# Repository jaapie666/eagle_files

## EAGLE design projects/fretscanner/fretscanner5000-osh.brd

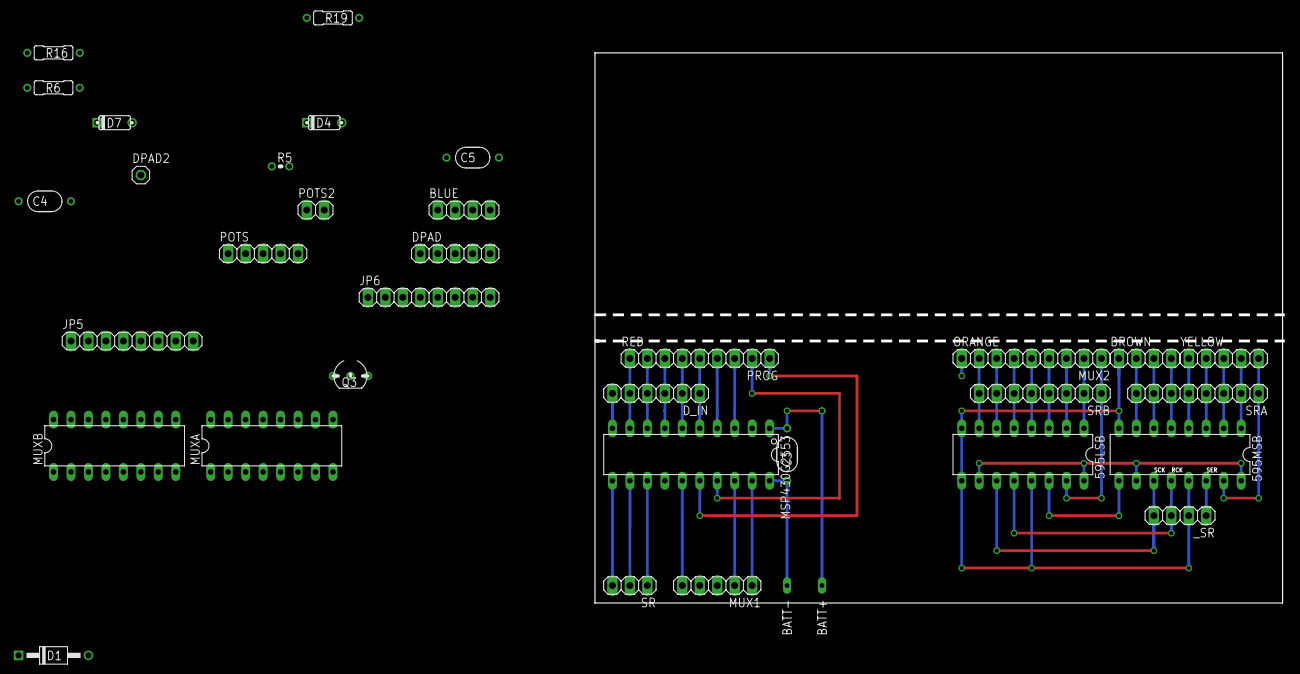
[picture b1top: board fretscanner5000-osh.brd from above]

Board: 2 copper layers, 100.0 x 80.0 mm, 37 parts (0 on the bottom side), 50 nets.

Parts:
595LSB, 595MSB: 74LS595N; DIL16
BATT+: LONG
BATT-: LONG
BLUE: 1X04
BROWN: 1X04
C3, C4, C5: 100n; 050X030_050_3
D1: DO41-4
D4, D7: 1N4148-2; DO35-2
DPAD: 1X05
DPAD2: 1X01
D_IN: 1X06
JP5, JP6: 1X08
MSP430G2553: G2XX3---N20; N20
MUX1: 1X05
MUX2: 1X04
MUXA: 4051N; DIL16
MUXB: 4051N; DIL16
ORANGE: 1X05
POTS: 1X05
POTS2: 1X02
PROG: 1X04
Q3: 2N3904; TO92-
R5: 300k; R0207/1V
R6: 1k; R0207/3
R16, R19: 30k; R0207/3
RED: 1X05
SR: 1X03
SRA: 1X08
SRB: 1X08
YELLOW: 1X05
_SR: 1X04

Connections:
D0: D_IN.1, MSP430G2553.5, RED.5
D1: D_IN.2, MSP430G2553.6, RED.4
D2: D_IN.3, MSP430G2553.7, RED.3
D3: D_IN.4, MSP430G2553.8, RED.2
D4: D_IN.5, MSP430G2553.9, RED.1
D5: D_IN.6, MSP430G2553.10, ORANGE.1
GND: 595LSB.8, 595LSB.13, 595MSB.8, 595MSB.13, BATT-.1, BROWN.1, C3.1, MSP430G2553.20
INH_A: MSP430G2553.18, MUX1.2
INH_B: MSP430G2553.19, MUX1.1
M_F1: 595MSB.1, SRA.2, YELLOW.4
M_F2: 595MSB.2, SRA.3, YELLOW.3
M_F3: 595MSB.3, SRA.4, YELLOW.2
M_F4: 595MSB.4, SRA.5, YELLOW.1
M_F5: 595LSB.4, ORANGE.5, SRB.5
M_F6: 595LSB.5, ORANGE.4, SRB.6
M_F7: 595LSB.6, ORANGE.3, SRB.7
M_F8: 595LSB.7, ORANGE.2, SRB.8
M_F9: 595MSB.5, BROWN.4, SRA.6
M_F10: 595MSB.15, SRA.1, YELLOW.5
M_F11: 595MSB.6, BROWN.3, SRA.7
M_F12: 595MSB.7, BROWN.2, SRA.8
unnamed: 595LSB.14, 595MSB.9
unnamed: 595LSB.15, MUX2.1, SRB.1
unnamed: 595LSB.1, MUX2.2, SRB.2
unnamed: 595LSB.2, MUX2.3, SRB.3
unnamed: Q3.2, R5.1, R6.2
unnamed: 595LSB.3, MUX2.4, SRB.4
unnamed: C5.1, MUXA.16
unnamed: D4.A, R16.2
unnamed: C4.1, MUXB.16
unnamed: D4.C, D7.C, R6.1
unnamed: C4.2, MUXB.7, MUXB.8
unnamed: C5.2, MUXA.7, MUXA.8
unnamed: Q3.3, R5.2
unnamed: D7.A, R19.2
unnamed: MSP430G2553.15, MUX1.5
unnamed: 595MSB.14, _SR.1
unnamed: 595LSB.11, 595MSB.11, _SR.4
unnamed: 595LSB.12, 595MSB.12, _SR.3
RCK: MSP430G2553.13, SR.1
RXD: MSP430G2553.3, PROG.3
SCK: MSP430G2553.12, SR.2
SER: MSP430G2553.11, SR.3
SR0: MUXA.11, MUXB.11
SR1: MUXA.10, MUXB.10
SR2: MUXA.9, MUXB.9
TEST: MSP430G2553.17, PROG.2
TXD: MSP430G2553.4, PROG.4
VA: 595LSB.10, 595LSB.16, 595MSB.10, 595MSB.16, BATT+.1, C3.2, MSP430G2553.1
_RST: MSP430G2553.16, PROG.1

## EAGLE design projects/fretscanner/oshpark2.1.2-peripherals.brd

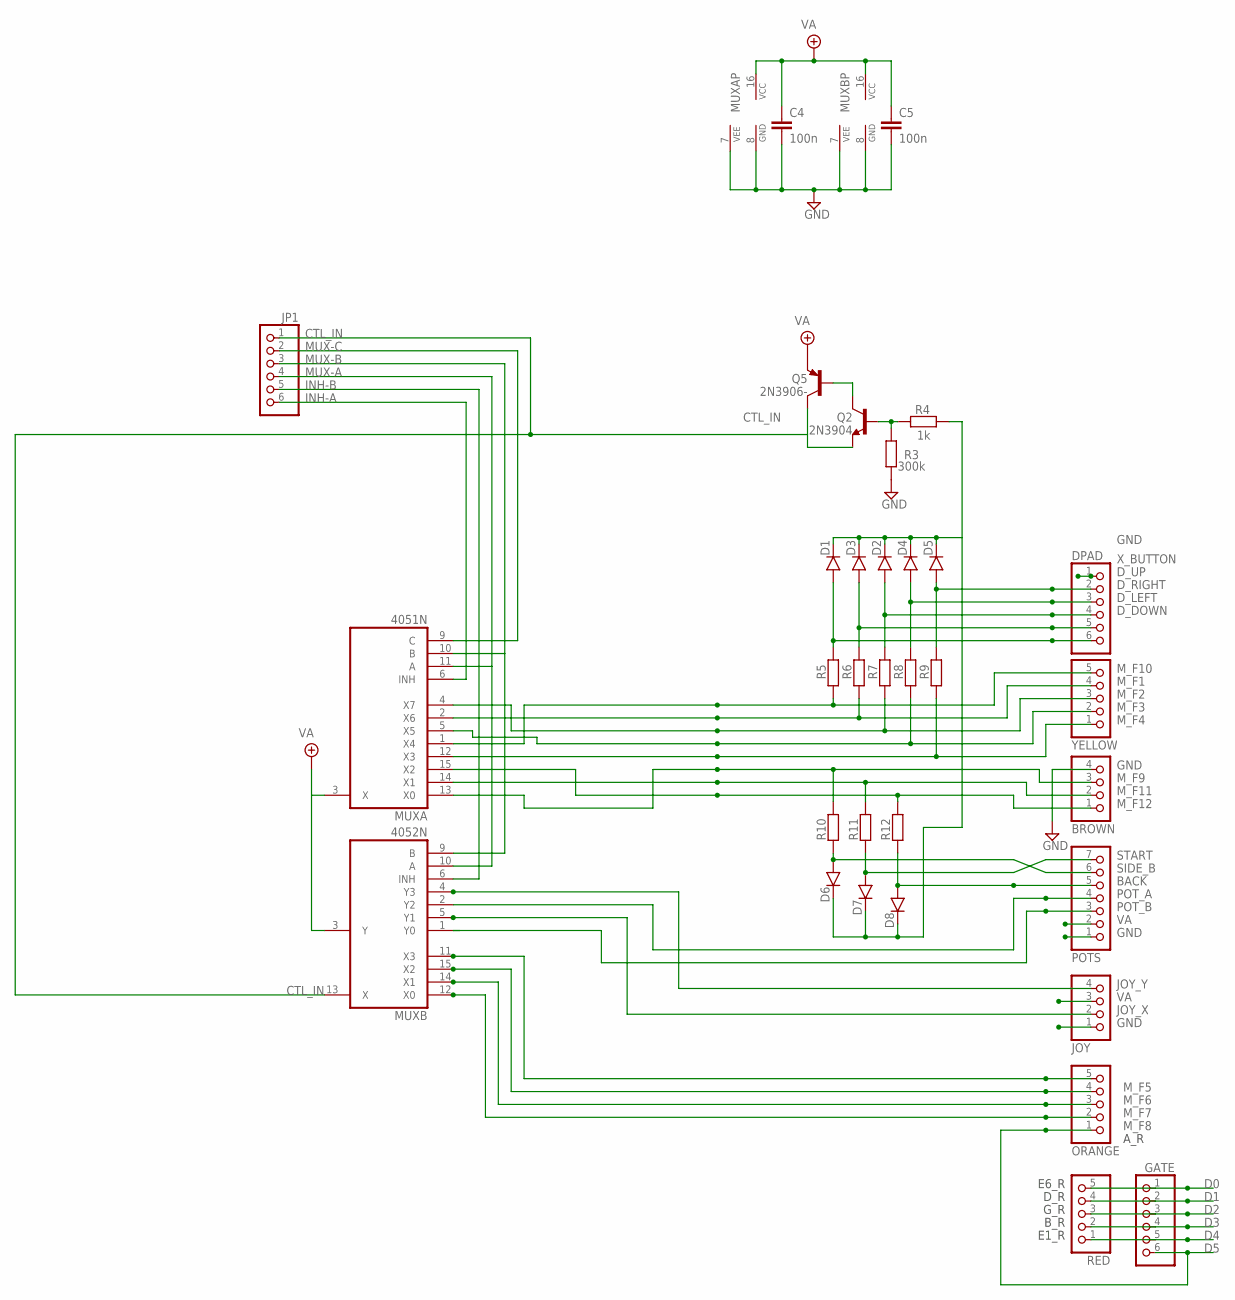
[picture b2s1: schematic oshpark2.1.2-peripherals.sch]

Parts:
BROWN: PINHD-1X4; 1X04
C4: 100n; 050X030_050_1
C5: 100n; 050X030_050_3
D1, D2, D3, D4, D5, D6, D7, D8: 1N4148-2; DO35-2
DPAD: PINHD-1X6; 1X06
GATE: PINHD-1X6; 1X06
JOY: PINHD-1X4; 1X04
JP1: PINHD-1X6; 1X06
MUXA: 4051N; DIL16
MUXB: 4052N; DIL16
ORANGE: PINHD-1X5; 1X05
POTS: PINHD-1X7; 1X07
Q2: 2N3904; TO92-
Q5: 2N3906-; TO92-
R3: 300k; R0207/1V
R4: 1k; R0207/3
R5, R6, R7, R8, R9: 30k; R0207/1V
R10, R11, R12: 30k; R0207/2V
RED: PINHD-1X5; 1X05
YELLOW: PINHD-1X5; 1X05

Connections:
BACK: D7.A, POTS.7, R11.2
CTL_IN: JP1.1, MUXB.13 (X), Q2.3 (E), Q5.1 (C)
D0: GATE.1, RED.5
D1: GATE.2, RED.4
D2: GATE.3, RED.3
D3: GATE.4, RED.2
D4: GATE.5, RED.1
D5: GATE.6, ORANGE.1
D_DOWN: D1.A, DPAD.6, R5.2
D_LEFT: D3.A, DPAD.5, R6.2
D_RIGHT: D2.A, DPAD.4, R7.2
D_UP: D4.A, DPAD.3, R8.2
GND: BROWN.4, C4.2, C5.2, DPAD.1, JOY.1, MUXA.7 (VEE), MUXA.8 (GND), MUXB.7 (VEE), MUXB.8 (GND), POTS.1, R3.2
INH-A: JP1.6, MUXA.6 (INH)
INH-B: JP1.5, MUXB.6 (INH)
JOY_X: JOY.2, MUXB.5 (Y1)
JOY_Y: JOY.4, MUXB.4 (Y3)
MUX-A: JP1.4, MUXA.11 (A), MUXB.10 (A)
MUX-B: JP1.3, MUXA.10 (B), MUXB.9 (B)
MUX-C: JP1.2, MUXA.9 (C)
M_F1: MUXA.2 (X6), R6.1, YELLOW.4
M_F2: MUXA.4 (X7), R7.1, YELLOW.3
M_F3: MUXA.5 (X5), R8.1, YELLOW.2
M_F4: MUXA.12 (X3), R9.1, YELLOW.1
M_F5: MUXB.11 (X3), ORANGE.5
M_F6: MUXB.15 (X2), ORANGE.4
M_F7: MUXB.14 (X1), ORANGE.3
M_F8: MUXB.12 (X0), ORANGE.2
M_F9: BROWN.3, MUXA.13 (X0), R10.1
M_F10: MUXA.1 (X4), R5.1, YELLOW.5
M_F11: BROWN.2, MUXA.14 (X1), R11.1
M_F12: BROWN.1, MUXA.15 (X2), R12.1
unnamed: Q2.1 (C), Q5.2 (B)
unnamed: Q2.2 (B), R3.1, R4.2
unnamed: D1.C, D2.C, D3.C, D4.C, D5.C, D6.C, D7.C, D8.C, R4.1
POT_A: MUXB.2 (Y2), POTS.4
POT_B: MUXB.1 (Y0), POTS.3
SIDE_B: D6.A, POTS.6, R10.2
START: D8.A, POTS.5, R12.2
VA: C4.1, C5.1, JOY.3, MUXA.3 (X), MUXA.16 (VCC), MUXB.3 (Y), MUXB.16 (VCC), POTS.2, Q5.3 (E)
X_BUTTON: D5.A, DPAD.2, R9.2

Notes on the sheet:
E6_R
D_R
G_R
B_R
E1_R
A_R

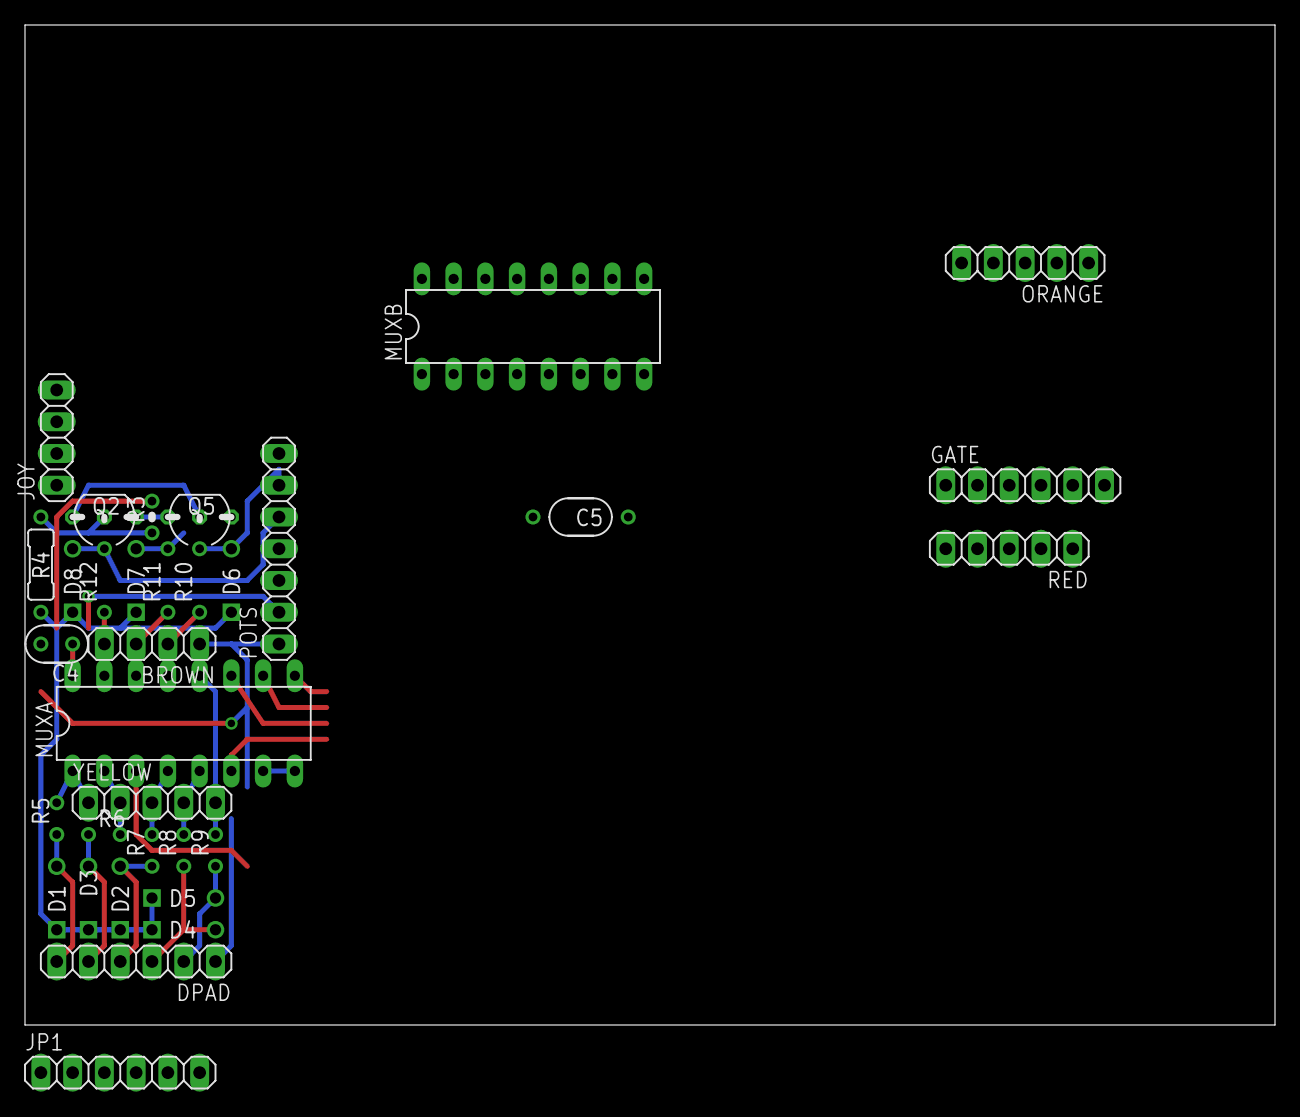
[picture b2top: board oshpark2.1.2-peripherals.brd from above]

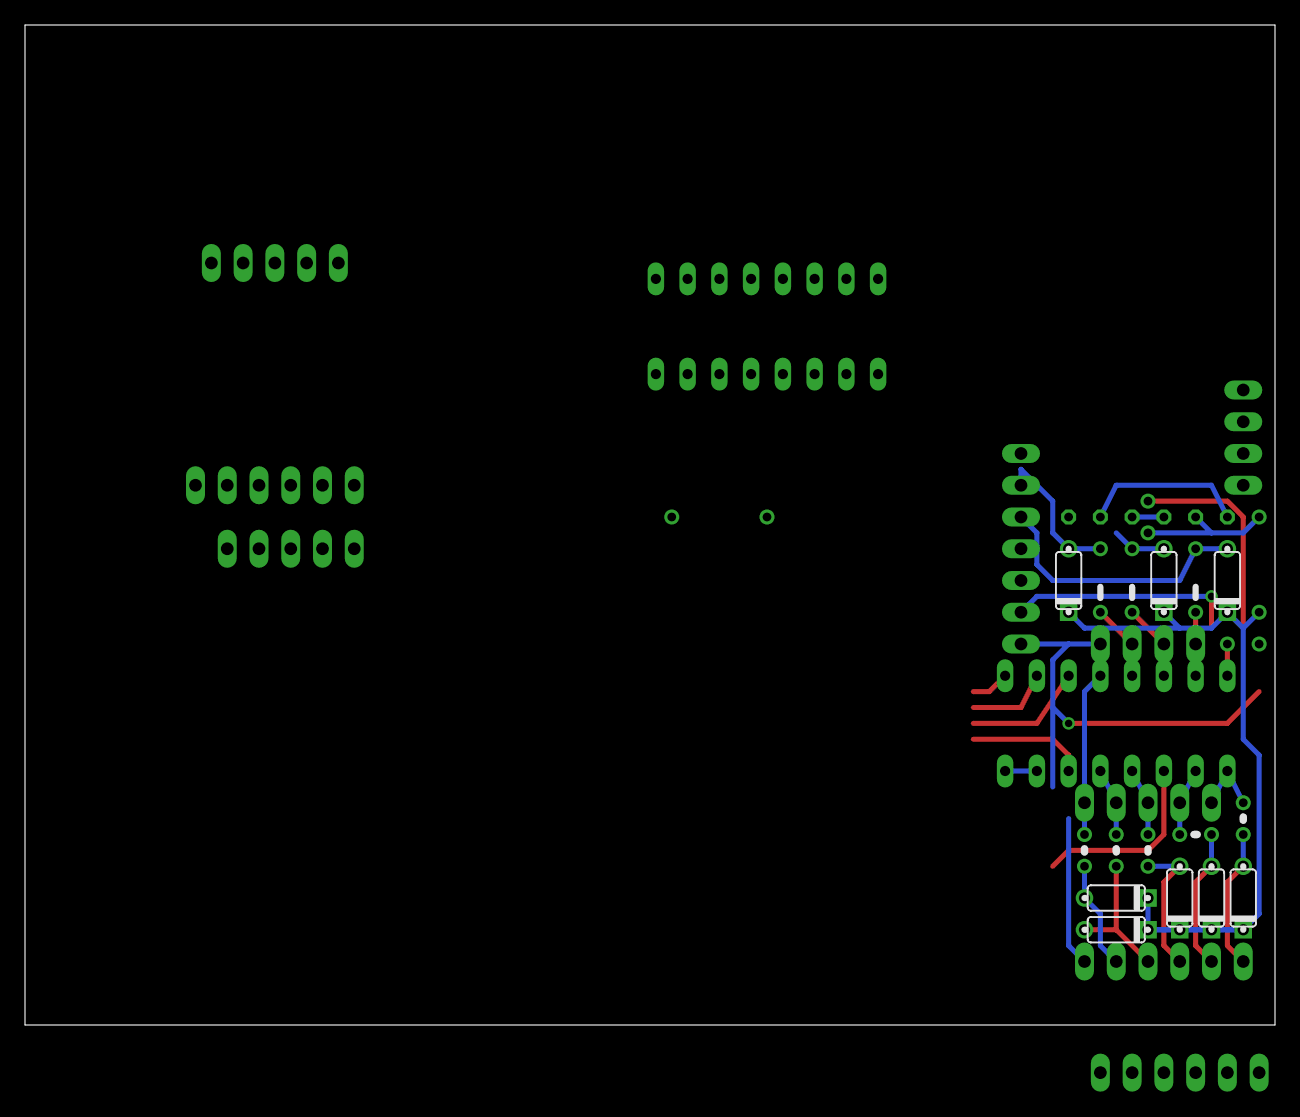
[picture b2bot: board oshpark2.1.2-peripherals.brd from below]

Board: 2 copper layers, 100.0 x 80.0 mm, 33 parts (16 on the bottom side), 41 nets.

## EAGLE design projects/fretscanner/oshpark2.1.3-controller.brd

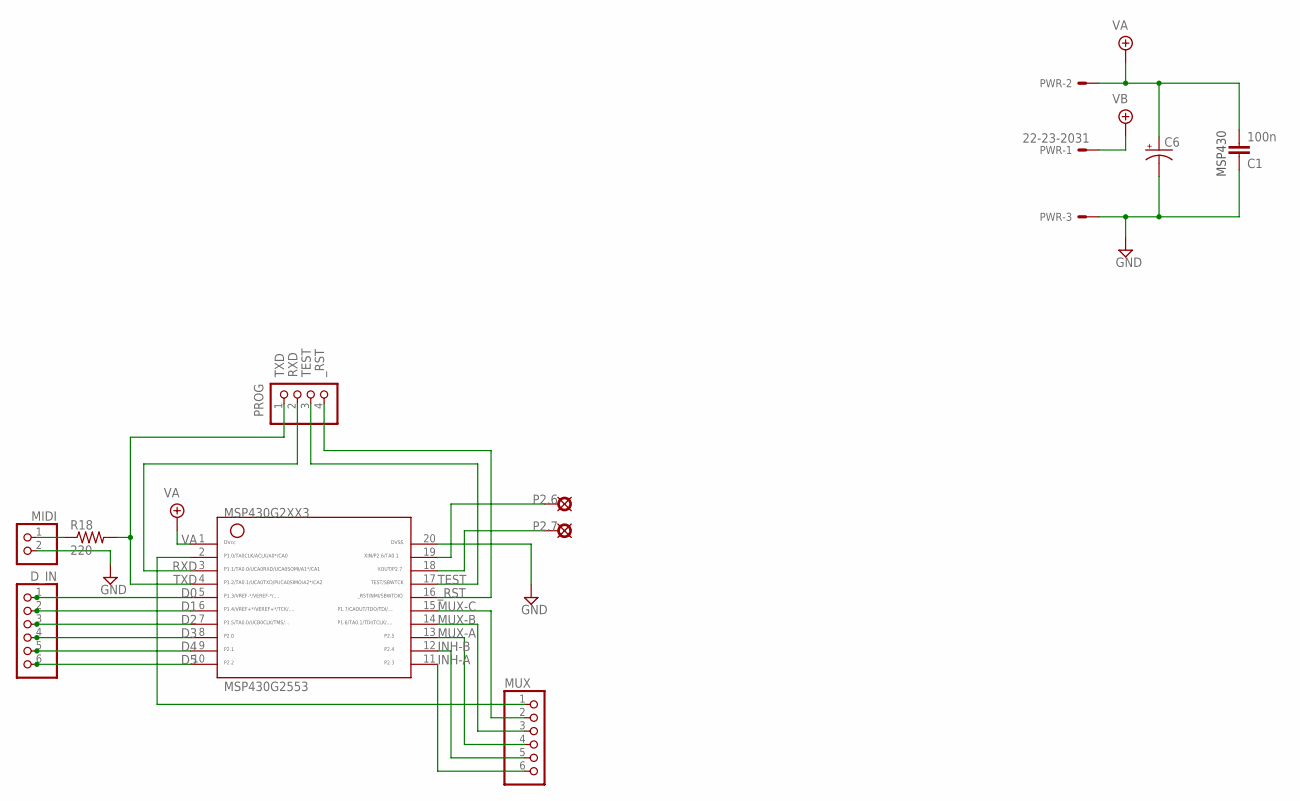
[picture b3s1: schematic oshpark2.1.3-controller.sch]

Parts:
C1: 100n; 050X030_050_3
C6: 0503; 050_020_3
D_IN: PINHD-1X6; 1X06
MIDI: PINHD-1X2; 1X02
MSP430G2553: G2XX3---N20; N20
MUX: PINHD-1X6; 1X06
P2.6, P2.7: PAD; SQUARE
PROG: PINHD-1X4; 1X04
PWR: 22-23-2031
R18: 220; R0207/3

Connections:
D0: D_IN.1, MSP430G2553.5
D1: D_IN.2, MSP430G2553.6
D2: D_IN.3, MSP430G2553.7
D3: D_IN.4, MSP430G2553.8
D4: D_IN.5, MSP430G2553.9
D5: D_IN.6, MSP430G2553.10
GND: C1.1, C6.-, MIDI.2, MSP430G2553.20, PWR.3
INH-A: MSP430G2553.11, MUX.6
INH-B: MSP430G2553.12, MUX.5
MUX-A: MSP430G2553.13, MUX.4
MUX-B: MSP430G2553.14, MUX.3
MUX-C: MSP430G2553.15, MUX.2
unnamed: MIDI.1, R18.1
unnamed: MSP430G2553.2, MUX.1
unnamed: MSP430G2553.19, P2.6.1
unnamed: MSP430G2553.18, P2.7.1
RXD: MSP430G2553.3, PROG.2
TEST: MSP430G2553.17, PROG.3
TXD: MSP430G2553.4, PROG.1, R18.2
VA: C1.2, C6.+, MSP430G2553.1, PWR.2
VB: PWR.1
_RST: MSP430G2553.16, PROG.4

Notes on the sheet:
MSP430

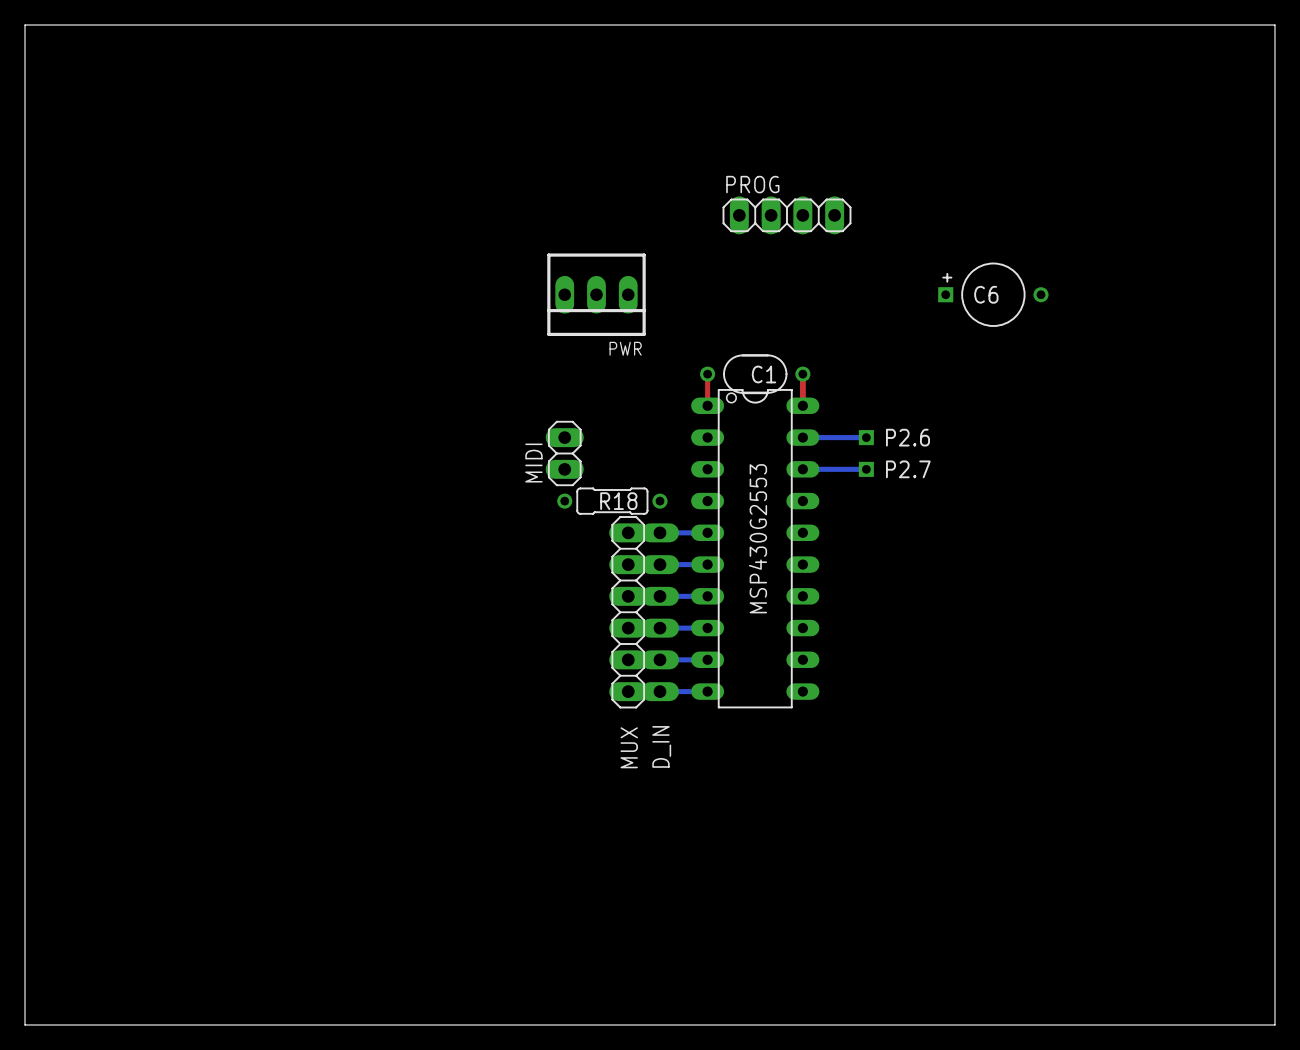
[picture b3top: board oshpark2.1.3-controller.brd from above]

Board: 2 copper layers, 100.0 x 80.0 mm, 11 parts (1 on the bottom side), 21 nets.

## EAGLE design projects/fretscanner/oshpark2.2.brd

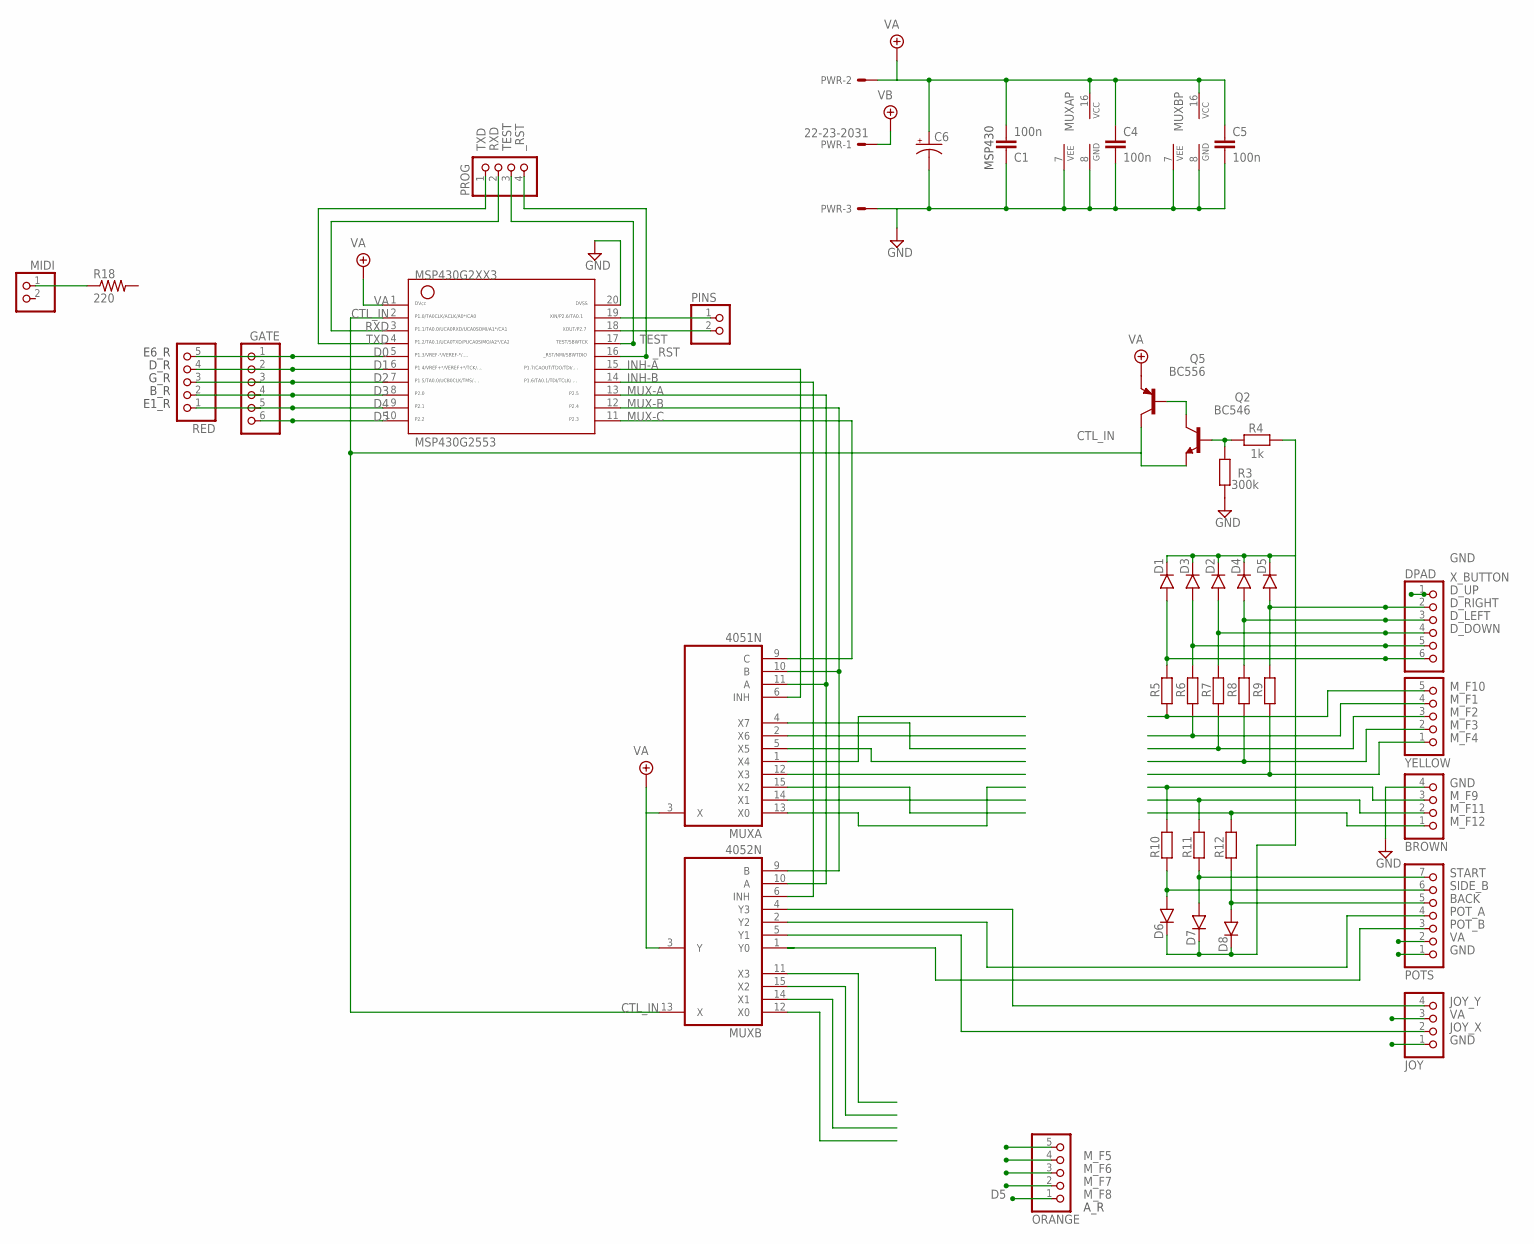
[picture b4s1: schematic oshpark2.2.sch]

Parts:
BROWN: PINHD-1X4; 1X04
C1, C5: 100n; 050X030_050_3
C4: 100n; 050X030_050_1
C6: 0501; 050_020_1
D1, D2, D3, D4, D5, D6, D7, D8: 1N4148-2; DO35-2
DPAD: PINHD-1X6; 1X06
GATE: PINHD-1X6; 1X06
JOY: PINHD-1X4; 1X04
MIDI: PINHD-1X2; 1X02
MSP430G2553: G2XX3---N20; N20
MUXA: 4051N; DIL16
MUXB: 4052N; DIL16
ORANGE: PINHD-1X5; 1X05
PINS: PINHD-1X2; 1X02
POTS: PINHD-1X7; 1X07
PROG: PINHD-1X4; 1X04
PWR: 22-23-2031
Q2: BC546; TO92-EBC
Q5: BC556; TO92-EBC
R3: 300k; R0207/1V
R4: 1k; R0207/3
R5, R6, R7, R8, R9: 30k; R0207/1V
R10, R11, R12: 30k; R0207/2V
R18: 220; R0207/3
RED: PINHD-1X5; 1X05
YELLOW: PINHD-1X5; 1X05

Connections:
BACK: D7.A, POTS.7, R11.2
CTL_IN: MSP430G2553.2, MUXB.13 (X), Q2.E, Q5.C
D0: GATE.1, MSP430G2553.5, RED.5
D1: GATE.2, MSP430G2553.6, RED.4
D2: GATE.3, MSP430G2553.7, RED.3
D3: GATE.4, MSP430G2553.8, RED.2
D4: GATE.5, MSP430G2553.9, RED.1
D5: GATE.6, MSP430G2553.10, ORANGE.1
D_DOWN: D1.A, DPAD.6, R5.2
D_LEFT: D3.A, DPAD.5, R6.2
D_RIGHT: D2.A, DPAD.4, R7.2
D_UP: D4.A, DPAD.3, R8.2
GND: BROWN.4, C1.1, C4.2, C5.2, C6.-, DPAD.1, JOY.1, MSP430G2553.20, MUXA.7 (VEE), MUXA.8 (GND), MUXB.7 (VEE), MUXB.8 (GND), POTS.1, PWR.3, R3.2
INH-A: MSP430G2553.15, MUXA.6 (INH)
INH-B: MSP430G2553.14, MUXB.6 (INH)
JOY_X: JOY.2, MUXB.5 (Y1)
JOY_Y: JOY.4, MUXB.4 (Y3)
MUX-A: MSP430G2553.13, MUXA.11 (A), MUXB.10 (A)
MUX-B: MUXA.10 (B), MUXB.9 (B)
MUX-C: MUXA.9 (C)
M_F1: R6.1, YELLOW.4
M_F2: R7.1, YELLOW.3
M_F3: R8.1, YELLOW.2
M_F4: R9.1, YELLOW.1
M_F5: ORANGE.5
M_F6: ORANGE.4
M_F7: ORANGE.3
M_F8: ORANGE.2
M_F9: BROWN.3, R10.1
M_F10: R5.1, YELLOW.5
M_F11: BROWN.2, R11.1
M_F12: BROWN.1, R12.1
unnamed: MIDI.1, R18.1
unnamed: Q2.C, Q5.B
unnamed: Q2.B, R3.1, R4.2
unnamed: MSP430G2553.19, PINS.1
unnamed: MSP430G2553.18, PINS.2
unnamed: D1.C, D2.C, D3.C, D4.C, D5.C, D6.C, D7.C, D8.C, R4.1
POT_A: MUXB.2 (Y2), POTS.4
POT_B: MUXB.1 (Y0), POTS.3
RXD: MSP430G2553.3, PROG.2
SIDE_B: D6.A, POTS.6, R10.2
START: D8.A, POTS.5, R12.2
TEST: MSP430G2553.17, PROG.3
TXD: MSP430G2553.4, PROG.1
VA: C1.2, C4.1, C5.1, C6.+, JOY.3, MSP430G2553.1, MUXA.3 (X), MUXA.16 (VCC), MUXB.3 (Y), MUXB.16 (VCC), POTS.2, PWR.2, Q5.E
VB: PWR.1
X_BUTTON: D5.A, DPAD.2, R9.2
_RST: MSP430G2553.16, PROG.4

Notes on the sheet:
E6_R
D_R
G_R
B_R
E1_R
A_R
MSP430

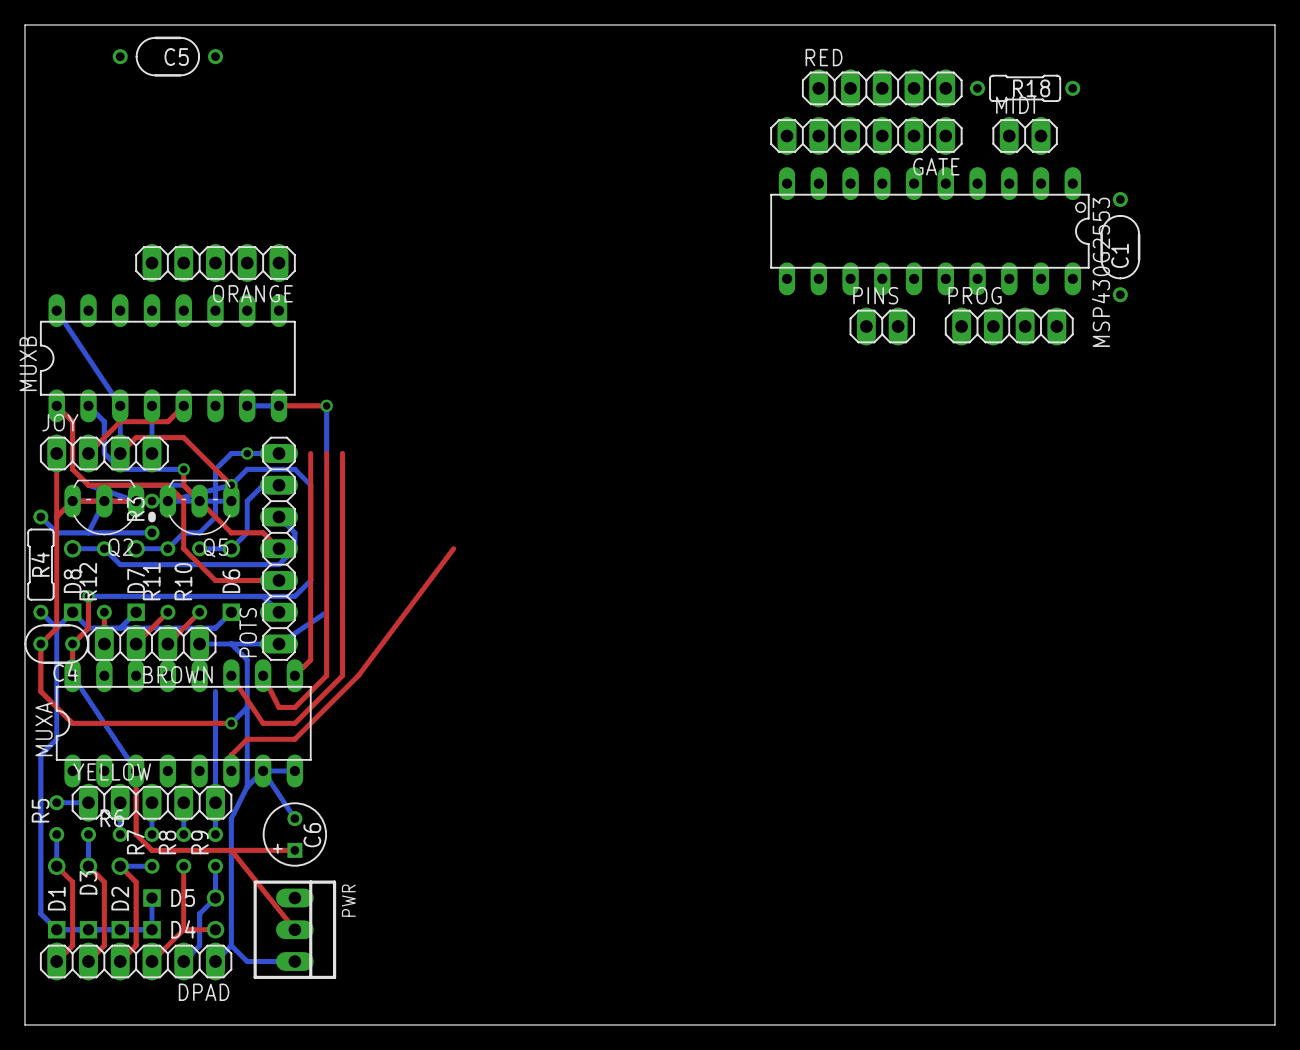
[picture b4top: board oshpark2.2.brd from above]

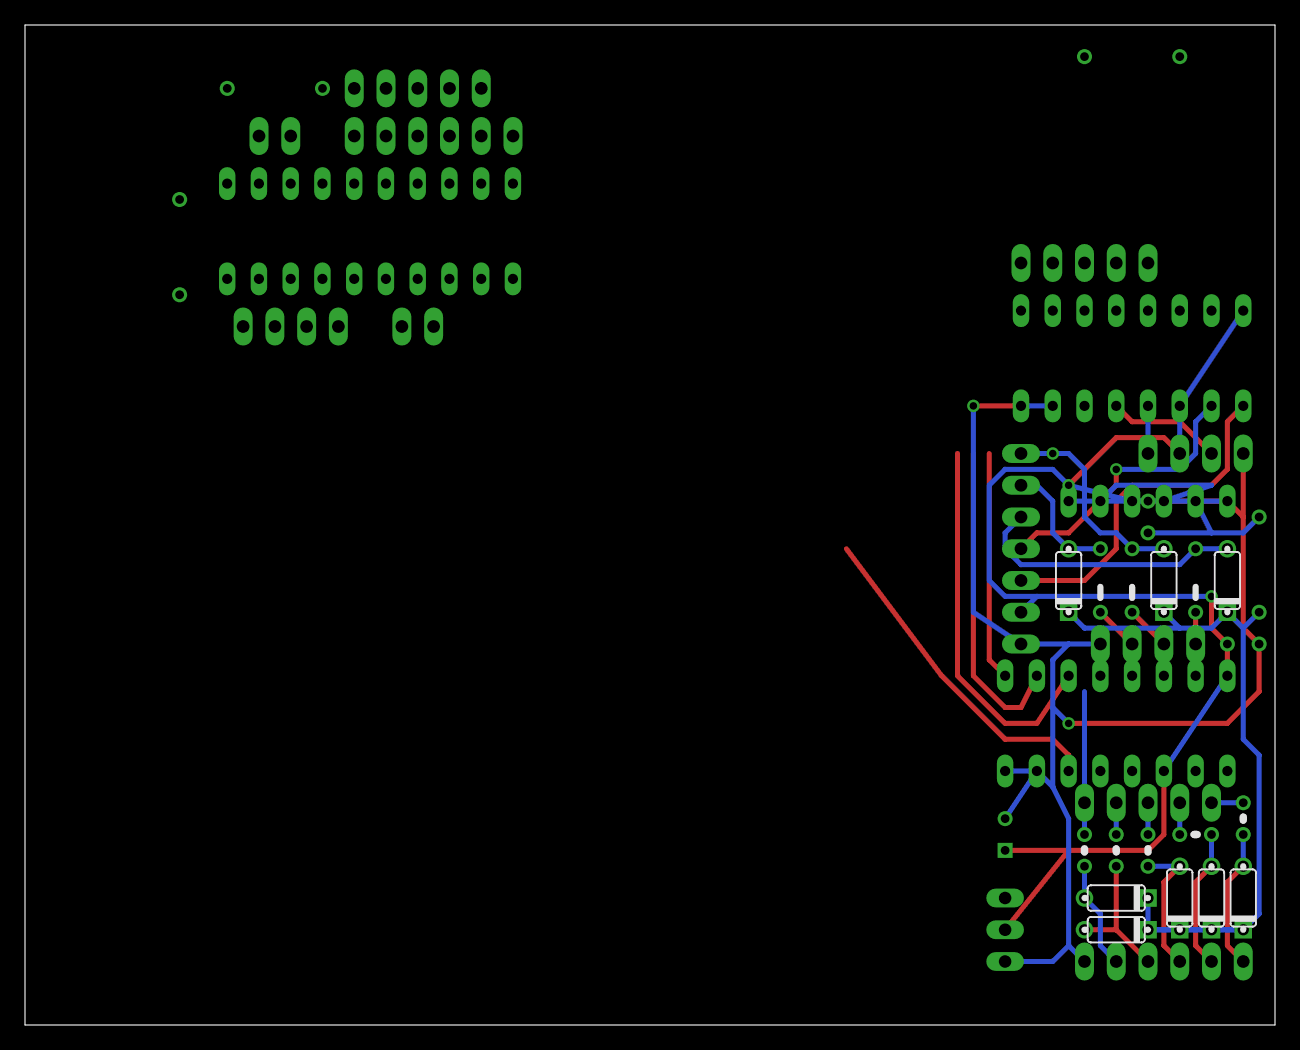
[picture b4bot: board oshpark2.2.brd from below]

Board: 2 copper layers, 100.0 x 80.0 mm, 40 parts (16 on the bottom side), 43 nets.

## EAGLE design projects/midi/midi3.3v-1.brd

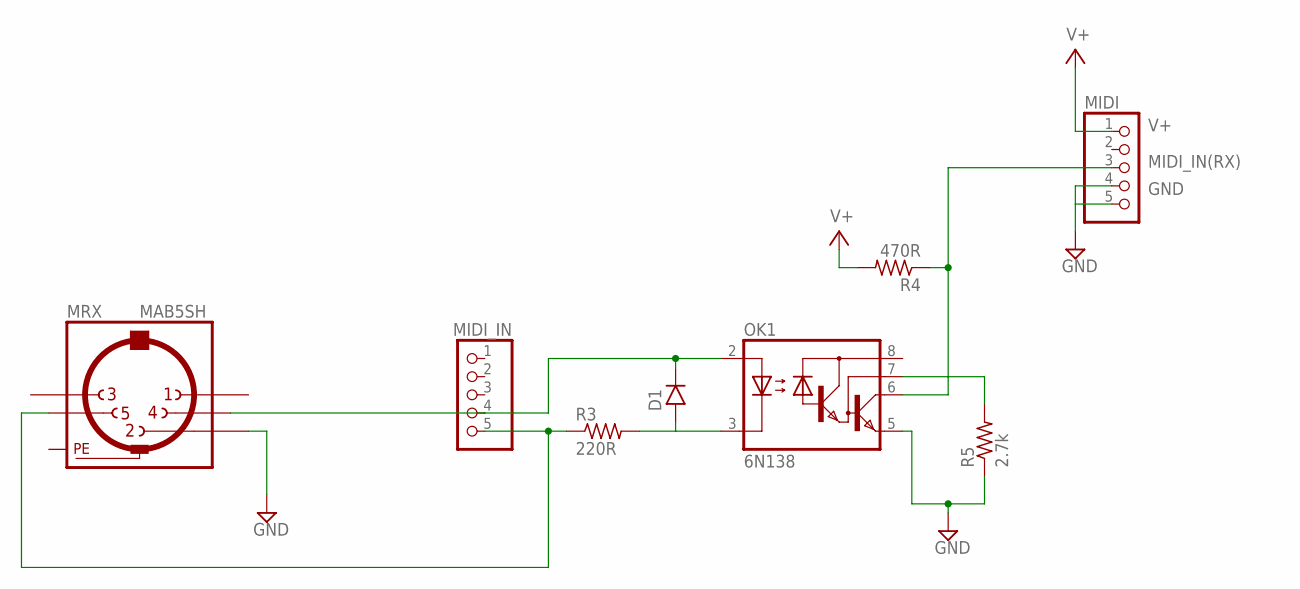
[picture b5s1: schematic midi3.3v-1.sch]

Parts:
D1: 1N4148-2; DO35-2
MIDI: PINHD-1X5; 1X05
MIDI_IN: PINHD-1X5; 1X05
MRX: MAB5SH
OK1: 6N138; DIL08
R3: 220R; R0207/3
R4: 470R; R0207/3
R5: 2.7k; R0207/3

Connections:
GND: MIDI.4, MIDI.5, MRX.2, OK1.5 (GND), R5.1
MIDI_IN(RX): MIDI.3, OK1.6 (VO), R4.1
unnamed: MIDI_IN.5, MRX.5, R3.1
unnamed: D1.A, OK1.3 (C), R3.2
unnamed: D1.C, MIDI_IN.4, MRX.4, OK1.2 (A)
unnamed: OK1.7 (VB), R5.2
PE: MRX.PE, MRX.PE@ (PE)
V+: MIDI.1, R4.2

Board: 2 copper layers, 8 parts (0 on the bottom side), 8 nets, no tracks yet.

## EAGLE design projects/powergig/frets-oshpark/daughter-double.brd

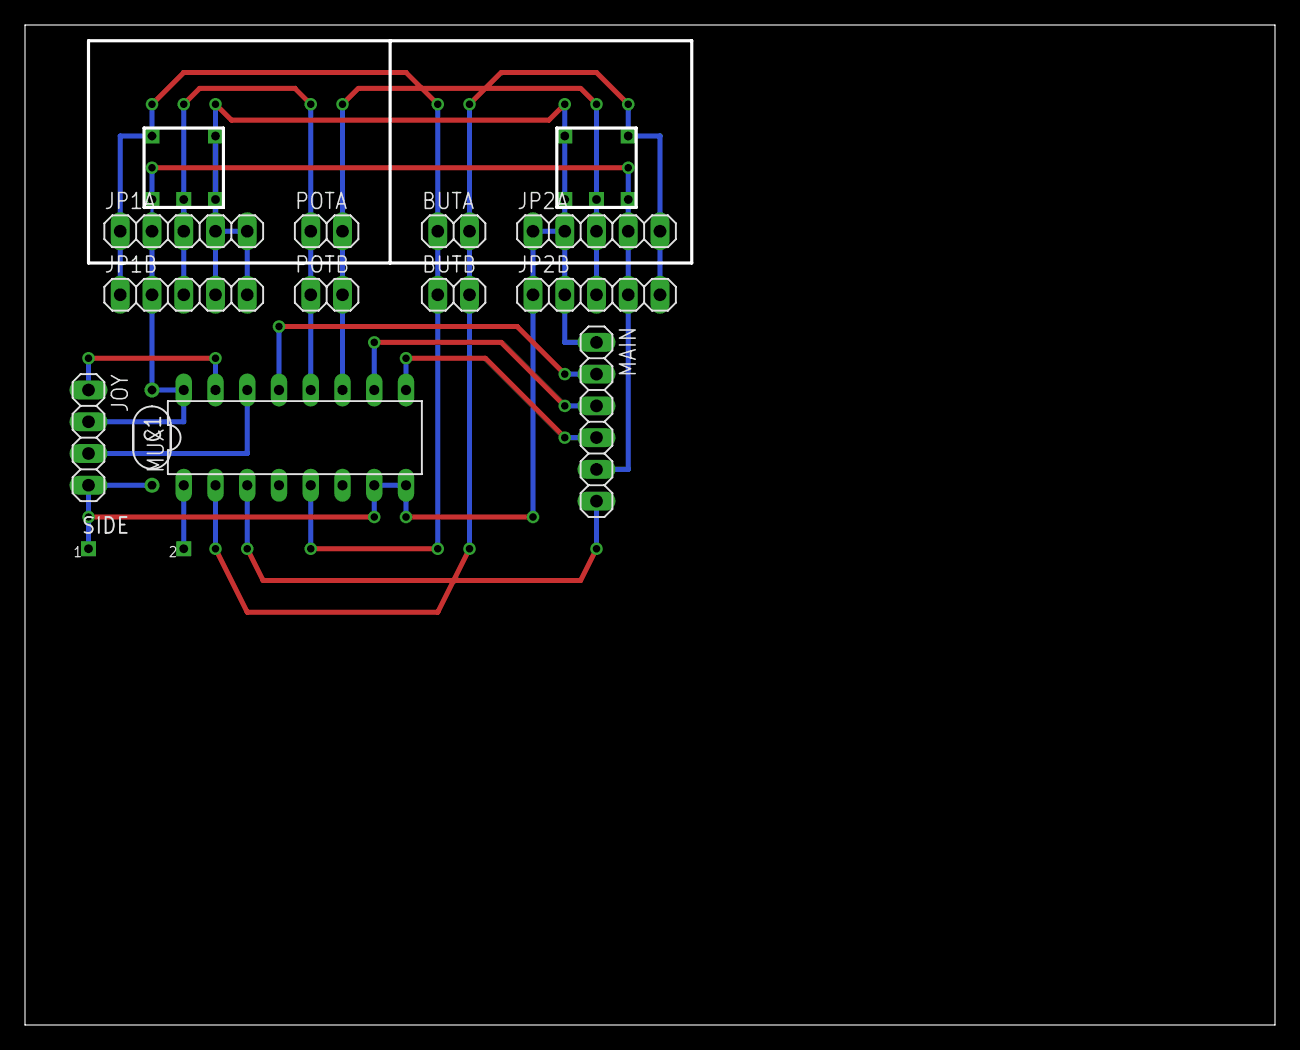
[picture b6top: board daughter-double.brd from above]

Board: 2 copper layers, 100.0 x 80.0 mm, 15 parts (0 on the bottom side), 13 nets.

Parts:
BACK1: SWPOT
BUTA: 1X02
BUTB: 1X02
C1: 100n; 050X030_050_3
JOY: 1X04
JP1A, JP1B, JP2A, JP2B: 1X05
MAIN: 1X06
MUX: 4052N; DIL16
POTA: 1X02
POTB: 1X02
SELECT1: SWPOT
SIDE: MOMENTARY; SPST2

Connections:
A: MAIN.4, MUX.9
B: MAIN.3, MUX.10
BSIDE: MUX.1, SIDE.2
BUTTA: BUTA.1, BUTB.1, JP1A.1, JP1B.1, MUX.5, SELECT1.SW_B
BUTTB: BACK1.SW_A, BUTA.2, BUTB.2, JP2A.5, JP2B.5, MUX.2
BUTTONS: MAIN.6, MUX.3
GND: BACK1.POT_B, BACK1.SW_B, C1.2, JOY.4, JP1A.4, JP1A.5, JP1B.4, JP1B.5, JP2A.1, JP2A.2, JP2B.1, JP2B.2, MAIN.1, MUX.7, MUX.8, SELECT1.POT_A, SELECT1.SW_A, SIDE.1
POTA: JP1A.3, JP1B.3, MUX.12, POTA.1, POTB.1, SELECT1.POT_W
POTB: BACK1.POT_W, JP2A.3, JP2B.3, MUX.11, POTA.2, POTB.2
POTS: MAIN.2, MUX.13
VA: BACK1.POT_A, C1.1, JOY.2, JP1A.2, JP1B.2, JP2A.4, JP2B.4, MAIN.5, MUX.16, SELECT1.POT_B
X: JOY.1, MUX.15
Y: JOY.3, MUX.14

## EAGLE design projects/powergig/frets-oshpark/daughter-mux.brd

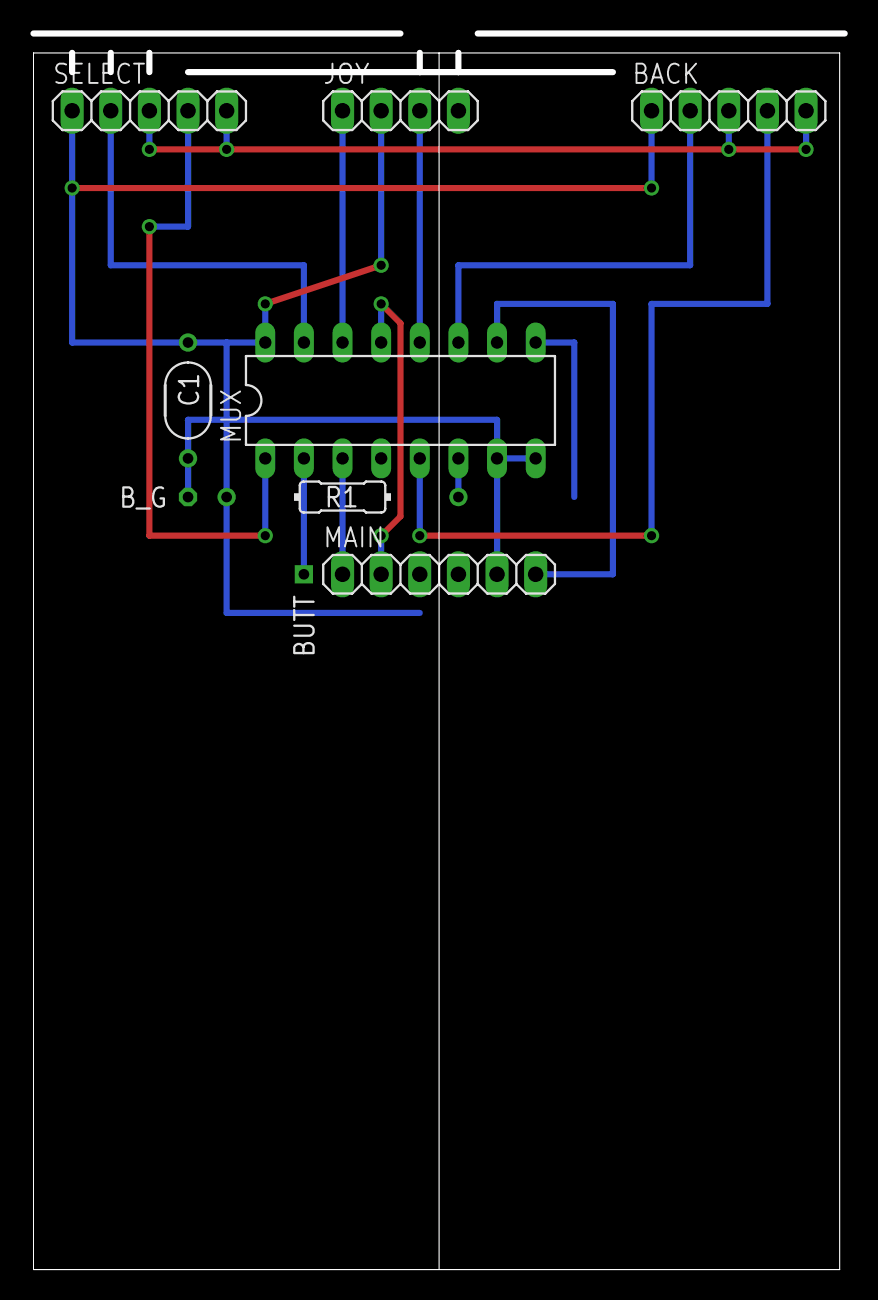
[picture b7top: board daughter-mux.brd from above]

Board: 2 copper layers, 53.3 x 81.3 mm, 9 parts (0 on the bottom side), 14 nets.

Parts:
BACK: 1X05
BUTT: SQUARE
B_G: OCTOGON
C1: 100n; 050X030_050_3
JOY: 1X04
MAIN: 1X06
MUX: 4052N; DIL16
R1: 10k; R0207/6
SELECT: 1X05

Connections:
A: MAIN.6, MUX.10
B: MAIN.4, MUX.9
BBACK: BACK.4, MUX.5
BSEL: MUX.1, SELECT.4
BSIDE: BUTT.1, MUX.2
BUTTONS: MAIN.1, MUX.3
GND: BACK.3, BACK.5, B_G.1, C1.2, JOY.4, MAIN.5, MUX.7, MUX.8, SELECT.3, SELECT.5
unnamed: MUX.6, R1.2
POTBACK: BACK.2, MUX.11
POTS: MAIN.2, MUX.13
POTSEL: MUX.15, SELECT.2
VA: BACK.1, C1.1, JOY.2, MAIN.3, MUX.16, R1.1, SELECT.1
X: JOY.1, MUX.14
Y: JOY.3, MUX.12
